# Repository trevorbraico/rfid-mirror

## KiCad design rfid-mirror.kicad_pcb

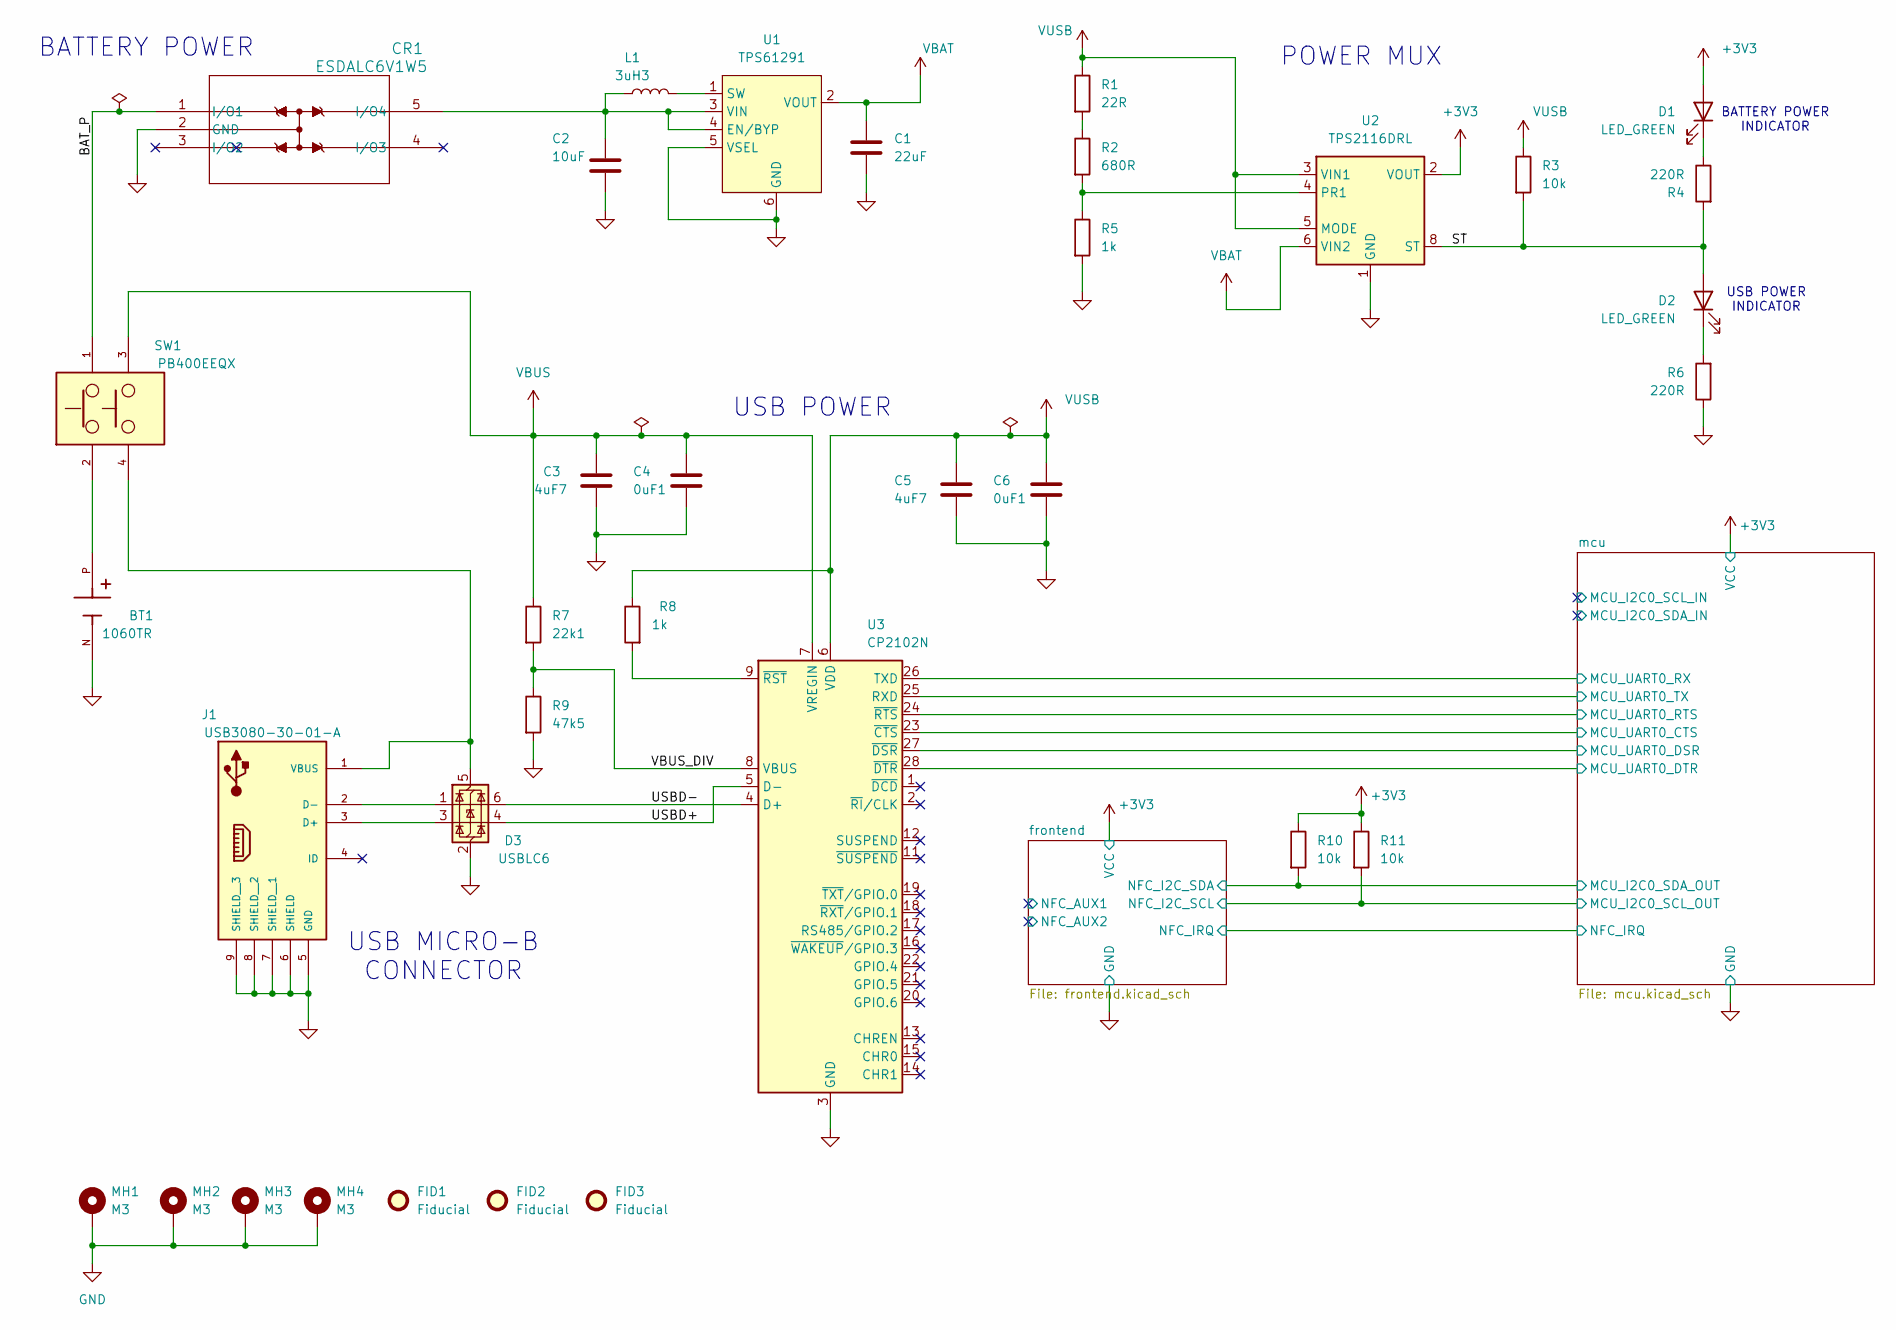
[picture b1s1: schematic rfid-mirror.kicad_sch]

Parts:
BT1: 1060TR; BAT_1060TR; PARTREV L; LCSC Part # C238069
C1: 22uF; C_0603_1608Metric; MPN CL10A226MP8NUNE; LCSC Part # C86295
C2: 10uF; C_0603_1608Metric; MPN CL10A106KP8NNNC; LCSC Part # C19702
C3, C5: 4uF7; C_0603_1608Metric; MPN CL10A475KO8NNNC; LCSC Part # C19666
C4, C6: 0uF1; C_0603_1608Metric; MPN CL10B104KB8NNNC; LCSC Part # C1591
CR1: ESDALC6V1W5; SOT323-5L_STM; MPN ESDALC6V1W5; LCSC Part # C703691
D1, D2: LED_GREEN; LED_0603_1608Metric; MPN SML-E12P8WT86; LCSC Part # C126319
D3: USBLC6; SOT-23-6; MPN USBLC6-2SC6; LCSC Part # C7519
FID1, FID2, FID3: Fiducial; Fiducial_1mm_Mask2mm
J1: USB3080-30-01-A; CONN5_80-30-01-A_GCT; MPN USB3080-30-01-A; LCSC Part # C6007479
L1: 3uH3; L_0603_1608Metric; MPN MLF1608A3R3KTA00; LCSC Part # C574026
MH1, MH2, MH3, MH4: M3; MountingHole_3.2mm_M3_Pad_Via
R1: 22R; R_0603_1608Metric; MPN RC0603FR-0722RL; LCSC Part # C107701
R2: 680R; R_0603_1608Metric; MPN RC0603FR-07680RL; LCSC Part # C112310
R3, R10, R11: 10k; R_0603_1608Metric; MPN RC0603FR-0710KL; LCSC Part # C98220
R4, R6: 220R; R_0603_1608Metric; MPN RC0603FR-07220RL; LCSC Part # C107696
R5, R8: 1k; R_0603_1608Metric; MPN RC0603JR-071KL; LCSC Part # C14676
R7: 22k1; R_0603_1608Metric; MPN RC0603FR-0722K1L; LCSC Part # C137768
R9: 47k5; R_0603_1608Metric; MPN RT0603BRE0747K5L; LCSC Part # C705859
SW1: PB400EEQX; SW_PB400EEQX; MPN PB400EEQX; LCSC Part # C5240796
U1: TPS61291; WSON-6-1EP_2x2mm_P0.65mm_EP1x1.6mm; MPN TPS61291DRVR; LCSC Part # C464809
U2: TPS2116DRL; SOT-583-8; MPN TPS2116DRLR; LCSC Part # C3235557
U3: CP2102N; QFN-28-1EP_5x5mm_P0.5mm_EP3.35x3.35mm; MPN CP2102N-A02-GQFN28R; LCSC Part # C964632

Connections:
+3V3: D1.2 (A), R10.1, R11.1, U2.2 (VOUT), U2.7 (VOUT); also elsewhere on the board
/BAT_P: CR1.1 (I/O1), SW1.1
/ST: D2.2 (A), R3.2, R4.1, U2.8 (ST)
/USBD+: D3.4 (I/O2), U3.5 (D-)
/USBD-: D3.6 (I/O1), U3.4 (D+)
/VBUS_DIV: R7.2, R9.1, U3.8 (VBUS)
/frontend/NFC_I2C_SCL: R11.2; also elsewhere on the board
/frontend/NFC_I2C_SDA: R10.2; also elsewhere on the board
/mcu/MCU_UART0_CTS: U3.23 (~CTS); also elsewhere on the board
/mcu/MCU_UART0_DSR: U3.27 (~DSR); also elsewhere on the board
/mcu/MCU_UART0_DTR: U3.28 (~DTR); also elsewhere on the board
/mcu/MCU_UART0_RTS: U3.24 (~RTS); also elsewhere on the board
/mcu/MCU_UART0_RX: U3.26 (TXD); also elsewhere on the board
/mcu/MCU_UART0_TX: U3.25 (RXD); also elsewhere on the board
GND: BT1.N, C1.2, C2.2, C3.2, C4.2, C5.2, C6.2, CR1.2 (GND), D3.2 (GND), J1.5 (GND), J1.6 (SHIELD), J1.7 (SHIELD__1), J1.8 (SHIELD__2), J1.9 (SHIELD__3), MH1.1, MH2.1, MH3.1, MH4.1, R5.2, R6.2, R9.2, U1.5 (VSEL), U1.6 (GND), U2.1 (GND), U3.3 (GND), U3.29 (GND); also elsewhere on the board
unnamed: BT1.P, SW1.2
unnamed: C2.1, CR1.5 (I/O4), L1.1, U1.3 (VIN), U1.4 (EN/BYP)
unnamed: D1.1 (K), R4.2
unnamed: D2.1 (K), R6.1
unnamed: D3.5 (VBUS), J1.1 (VBUS), SW1.4
unnamed: D3.3 (I/O2), J1.3 (D+)
unnamed: D3.1 (I/O1), J1.2 (D-)
unnamed: R1.2, R2.1
unnamed: L1.2, U1.1 (SW)
unnamed: R2.2, R5.1, U2.4 (PR1)
unnamed: R8.2, U3.9 (~RST)
VBAT: C1.1, U1.2 (VOUT), U2.6 (VIN2)
VBUS: C3.1, C4.1, R7.1, SW1.3, U3.7 (VREGIN)
VUSB: C5.1, C6.1, R1.1, R3.1, R8.1, U2.3 (VIN1), U2.5 (MODE), U3.6 (VDD)

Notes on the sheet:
POWER MUX
USB POWER
USB MICRO-B CONNECTOR
BATTERY POWER
USB POWER INDICATOR
BATTERY POWER INDICATOR

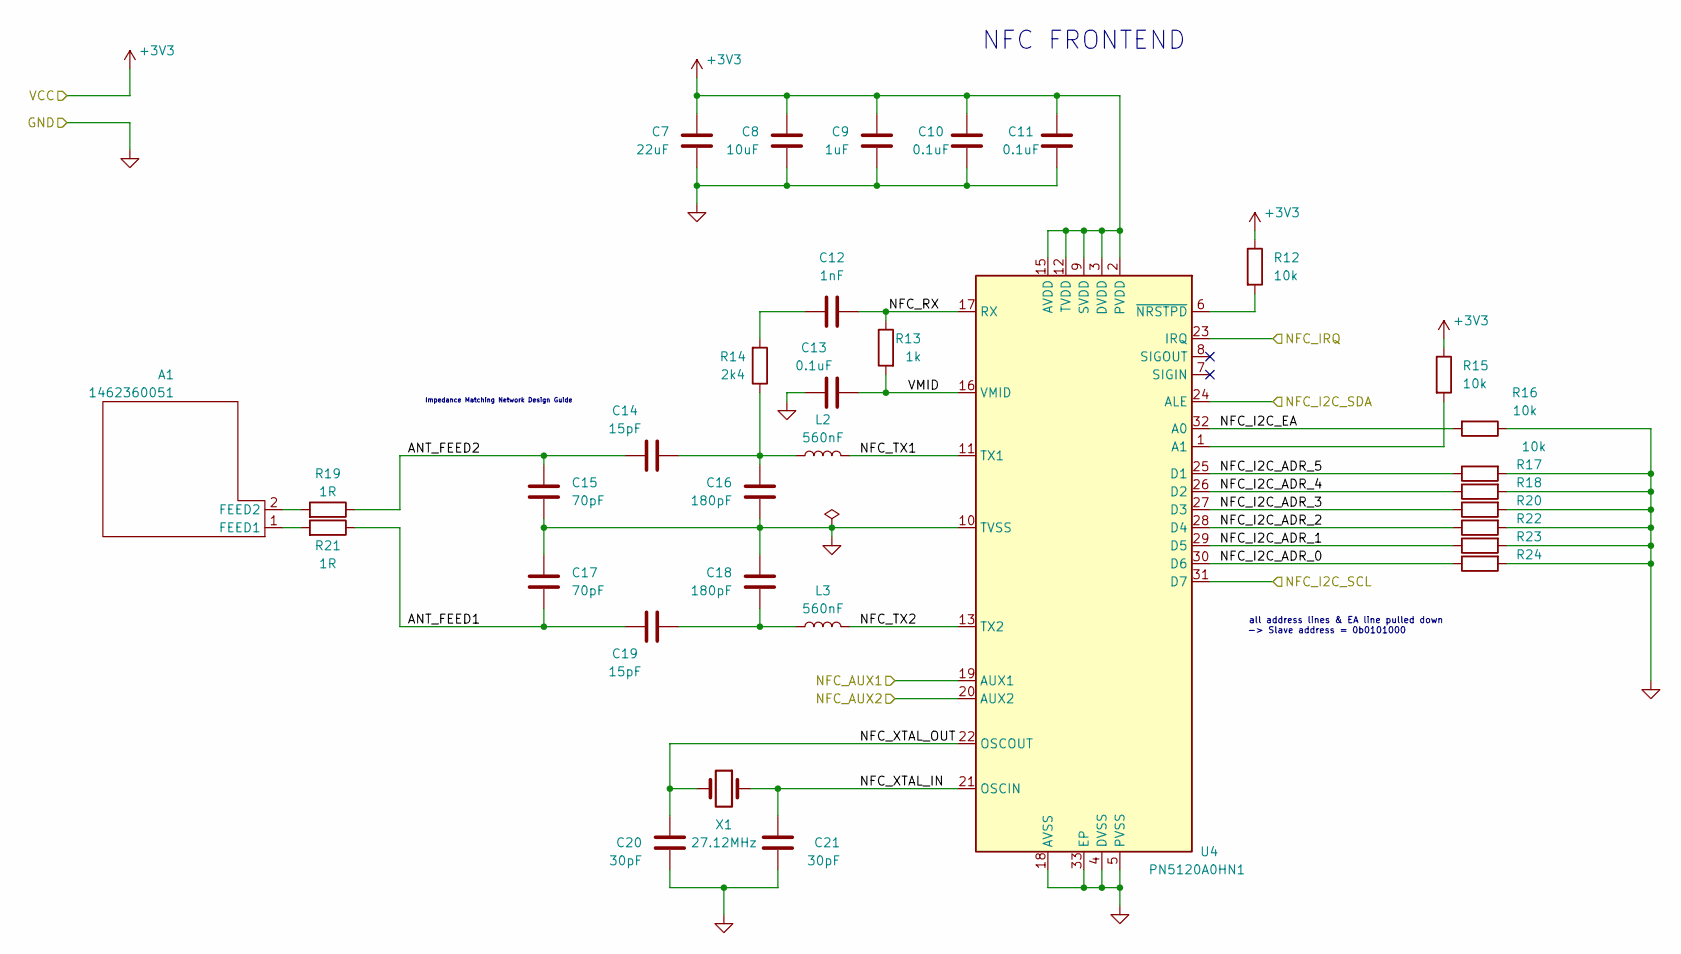
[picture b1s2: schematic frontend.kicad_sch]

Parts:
A1: 1462360051; 1462360101 RFID Antenna; MPN 1462360051; LCSC Part # C3284867
C7: 22uF; C_0603_1608Metric; MPN CL10A226MP8NUNE; LCSC Part # C86295
C8: 10uF; C_0603_1608Metric; MPN CL10A106KP8NNNC; LCSC Part # C19702
C9: 1uF; C_0603_1608Metric; MPN CL10A105KB8NNNC; LCSC Part # C15849
C10, C11, C13: 0.1uF; C_0603_1608Metric; MPN CL10B104KB8NNNC; LCSC Part # C1591
C12: 1nF; C_0603_1608Metric; MPN CL10C102JB8NNNC; LCSC Part # C163508
C14, C19: 15pF; C_0603_1608Metric; MPN CC0603GRNPO9BN150; LCSC Part # C519451
C15, C17: 70pF; C_0603_1608Metric; MPN MA0603CG700G500; LCSC Part # C3851853
C16, C18: 180pF; C_0603_1608Metric; MPN CC0603JRNPO9BN181; LCSC Part # C107041
C20, C21: 30pF; C_0603_1608Metric; MPN CC0603JRNPO9BN300; LCSC Part # C113797
L2, L3: 560nF; L_0603_1608Metric; MPN LQW18CNR56J00D; LCSC Part # C91630
R12, R15, R16, R17, R18, R20, R22, R23, R24: 10k; R_0603_1608Metric; MPN RC0603FR-0710KL; LCSC Part # C98220
R13: 1k; R_0603_1608Metric; MPN RC0603JR-071KL; LCSC Part # C14676
R14: 2k4; R_0603_1608Metric; MPN RC0603JR-072K4L; LCSC Part # C127450
R19, R21: 1R; R_0603_1608Metric; MPN RC0603JR-071RL; LCSC Part # C127987
U4: PN5120A0HN1; HVQFN-32-1EP_5x5mm_P0.5mm_EP3.1x3.1mm; MPN PN5120A0HN1/C2,151; LCSC Part # C38659
X1: 27.12MHz; Crystal_SMD_3225-4Pin_3.2x2.5mm; MPN XL2EL89CSI-111YLC-27.12M; LCSC Part # C5444554

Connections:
+3V3: C7.1, C8.1, C9.1, C10.1, C11.1, R12.1, R15.1, U4.2 (PVDD), U4.3 (DVDD), U4.9 (SVDD), U4.12 (TVDD), U4.15 (AVDD); also elsewhere on the board
/frontend/ANT_FEED1: C17.2, C19.1, R21.1
/frontend/ANT_FEED2: C14.1, C15.1, R19.1
/frontend/NFC_AUX1: U4.19 (AUX1)
/frontend/NFC_AUX2: U4.20 (AUX2)
/frontend/NFC_I2C_ADR_0: R24.1, U4.30 (D6)
/frontend/NFC_I2C_ADR_1: R23.1, U4.29 (D5)
/frontend/NFC_I2C_ADR_2: R22.1, U4.28 (D4)
/frontend/NFC_I2C_ADR_3: R20.1, U4.27 (D3)
/frontend/NFC_I2C_ADR_4: R18.1, U4.26 (D2)
/frontend/NFC_I2C_ADR_5: R17.1, U4.25 (D1)
/frontend/NFC_I2C_EA: R16.2, U4.32 (A0)
/frontend/NFC_I2C_SCL: U4.31 (D7); also elsewhere on the board
/frontend/NFC_I2C_SDA: U4.24 (ALE); also elsewhere on the board
/frontend/NFC_IRQ: U4.23 (IRQ); also elsewhere on the board
/frontend/NFC_RX: C12.1, R13.1, U4.17 (RX)
/frontend/NFC_TX1: L2.1, U4.11 (TX1)
/frontend/NFC_TX2: L3.1, U4.13 (TX2)
/frontend/NFC_XTAL_IN: C21.1, U4.21 (OSCIN), X1.1
/frontend/NFC_XTAL_OUT: C20.1, U4.22 (OSCOUT), X1.2
/frontend/VMID: C13.1, R13.2, U4.16 (VMID)
GND: C7.2, C8.2, C9.2, C10.2, C11.2, C13.2, C15.2, C16.2, C17.1, C18.1, C20.2, C21.2, R16.1, R17.2, R18.2, R20.2, R22.2, R23.2, R24.2, U4.4 (DVSS), U4.5 (PVSS), U4.10 (TVSS), U4.18 (AVSS), U4.33 (EP); also elsewhere on the board
unnamed: A1.1 (FEED1), R21.2
unnamed: A1.2 (FEED2), R19.2
unnamed: C12.2, R14.2
unnamed: C14.2, C16.1, L2.2, R14.1
unnamed: C18.2, C19.2, L3.2
unnamed: R15.2, U4.1 (A1)
unnamed: R12.2, U4.6 (~NRSTPD)

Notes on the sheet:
all address lines & EA line pulled down -> Slave address = 0b0101000
Impedance Matching Network Design Guide
NFC FRONTEND

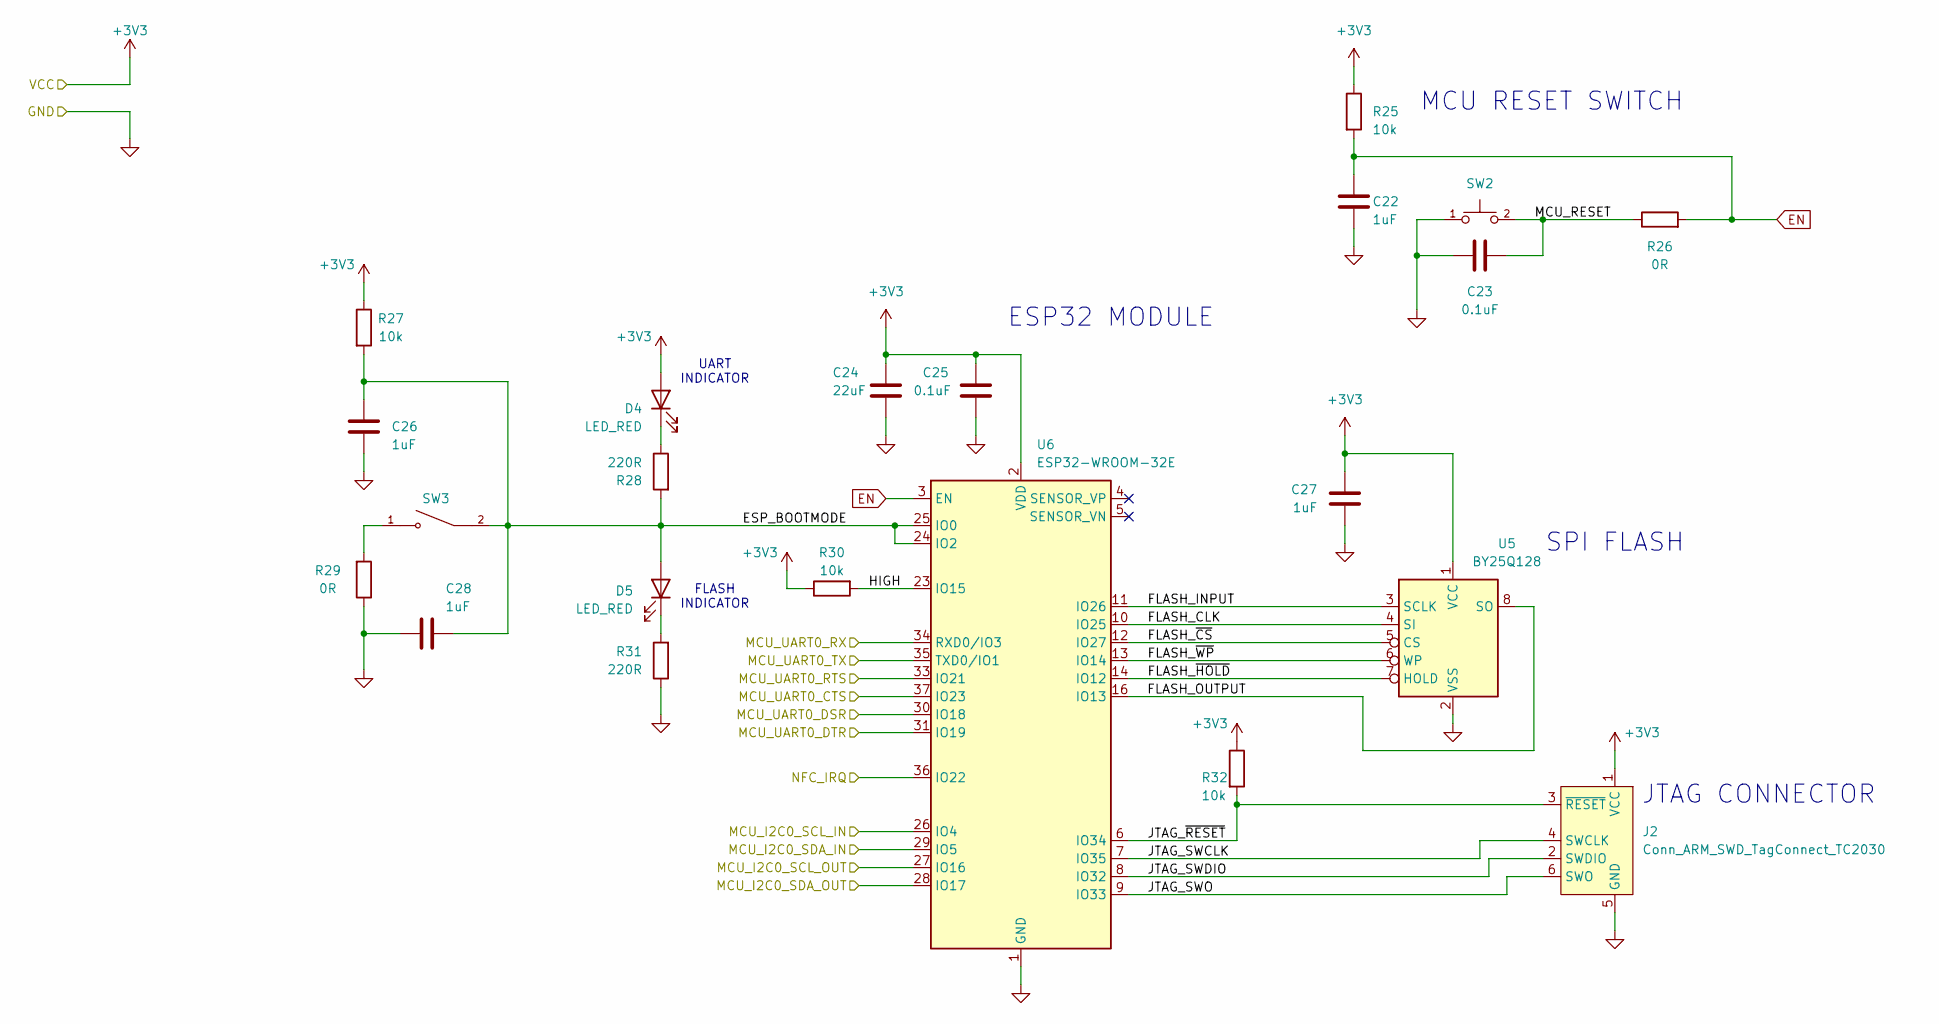
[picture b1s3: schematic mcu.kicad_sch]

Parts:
C22, C26, C27, C28: 1uF; C_0603_1608Metric; MPN CL10A105KB8NNNC; LCSC Part # C15849
C23, C25: 0.1uF; C_0603_1608Metric; MPN CL10B104KB8NNNC; LCSC Part # C1591
C24: 22uF; C_0603_1608Metric; MPN CL10A226MP8NUNE; LCSC Part # C86295
D4, D5: LED_RED; LED_0603_1608Metric; MPN SML-D12U8WT86C; LCSC Part # C2846640
J2: Conn_ARM_SWD_TagConnect_TC2030; Tag-Connect_TC2030-IDC-FP_2x03_P1.27mm_Vertical
R25, R27, R30, R32: 10k; R_0603_1608Metric; MPN RC0603FR-0710KL; LCSC Part # C98220
R26, R29: 0R; R_0603_1608Metric; MPN RC0603JR-070RL; LCSC Part # C105580
R28, R31: 220R; R_0603_1608Metric; MPN RC0603FR-07220RL; LCSC Part # C107696
SW2: B3U-1000P; SW_B3U-1000P; MPN B3U-1000P; LCSC Part # C231329
SW3: GF-123-0054; SW_GF-123-0054; MPN GF-123-0054; LCSC Part # C3029861
U5: BY25Q128; SOIC-8_5.3x5.3mm_P1.27mm; MPN BY25Q128ESSIG(T); LCSC Part # C22471255
U6: ESP32-WROOM-32E; MPN ESP32-WROOM-32E-N4; LCSC Part # C701341

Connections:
+3V3: C24.1, C25.1, C27.1, D4.2 (A), J2.1 (VCC), R25.1, R27.1, R30.1, R32.1, U5.1 (VCC), U6.2 (VDD); also elsewhere on the board
/frontend/NFC_I2C_SCL: U6.27 (IO16); also elsewhere on the board
/frontend/NFC_I2C_SDA: U6.28 (IO17); also elsewhere on the board
/frontend/NFC_IRQ: U6.36 (IO22); also elsewhere on the board
/mcu/ESP_BOOTMODE: C26.1, C28.2, D5.2 (A), R27.2, R28.1, SW3.2, U6.24 (IO2), U6.25 (IO0)
/mcu/FLASH_CLK: U5.4 (SI), U6.10 (IO25)
/mcu/FLASH_INPUT: U5.3 (SCLK), U6.11 (IO26)
/mcu/FLASH_OUTPUT: U5.8 (SO), U6.16 (IO13)
/mcu/FLASH_~CS: U5.5 (CS), U6.12 (IO27)
/mcu/FLASH_~HOLD: U5.7 (HOLD), U6.14 (IO12)
/mcu/FLASH_~WP: U5.6 (WP), U6.13 (IO14)
/mcu/HIGH: R30.2, U6.23 (IO15)
/mcu/JTAG_SWCLK: J2.4 (SWCLK), U6.7 (IO35)
/mcu/JTAG_SWDIO: J2.2 (SWDIO), U6.8 (IO32)
/mcu/JTAG_SWO: J2.6 (SWO), U6.9 (IO33)
/mcu/JTAG_~RESET: J2.3 (~RESET), R32.2, U6.6 (IO34)
/mcu/MCU_I2C0_SCL_IN: U6.26 (IO4)
/mcu/MCU_I2C0_SDA_IN: U6.29 (IO5)
/mcu/MCU_RESET: C23.1, R26.1, SW2.2
/mcu/MCU_UART0_CTS: U6.37 (IO23); also elsewhere on the board
/mcu/MCU_UART0_DSR: U6.30 (IO18); also elsewhere on the board
/mcu/MCU_UART0_DTR: U6.31 (IO19); also elsewhere on the board
/mcu/MCU_UART0_RTS: U6.33 (IO21); also elsewhere on the board
/mcu/MCU_UART0_RX: U6.34 (RXD0/IO3); also elsewhere on the board
/mcu/MCU_UART0_TX: U6.35 (TXD0/IO1); also elsewhere on the board
EN: C22.1, R25.2, R26.2, U6.3 (EN)
GND: C22.2, C23.2, C24.2, C25.2, C26.2, C27.2, C28.1, J2.5 (GND), R29.1, R31.2, SW2.1, U5.2 (VSS), U6.1 (GND), U6.15 (GND), U6.38 (GND), U6.39 (GND); also elsewhere on the board
unnamed: D4.1 (K), R28.2
unnamed: D5.1 (K), R31.1
unnamed: R29.2, SW3.1

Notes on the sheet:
SPI FLASH
UART INDICATOR
MCU RESET SWITCH
ESP32 MODULE
JTAG CONNECTOR
FLASH INDICATOR

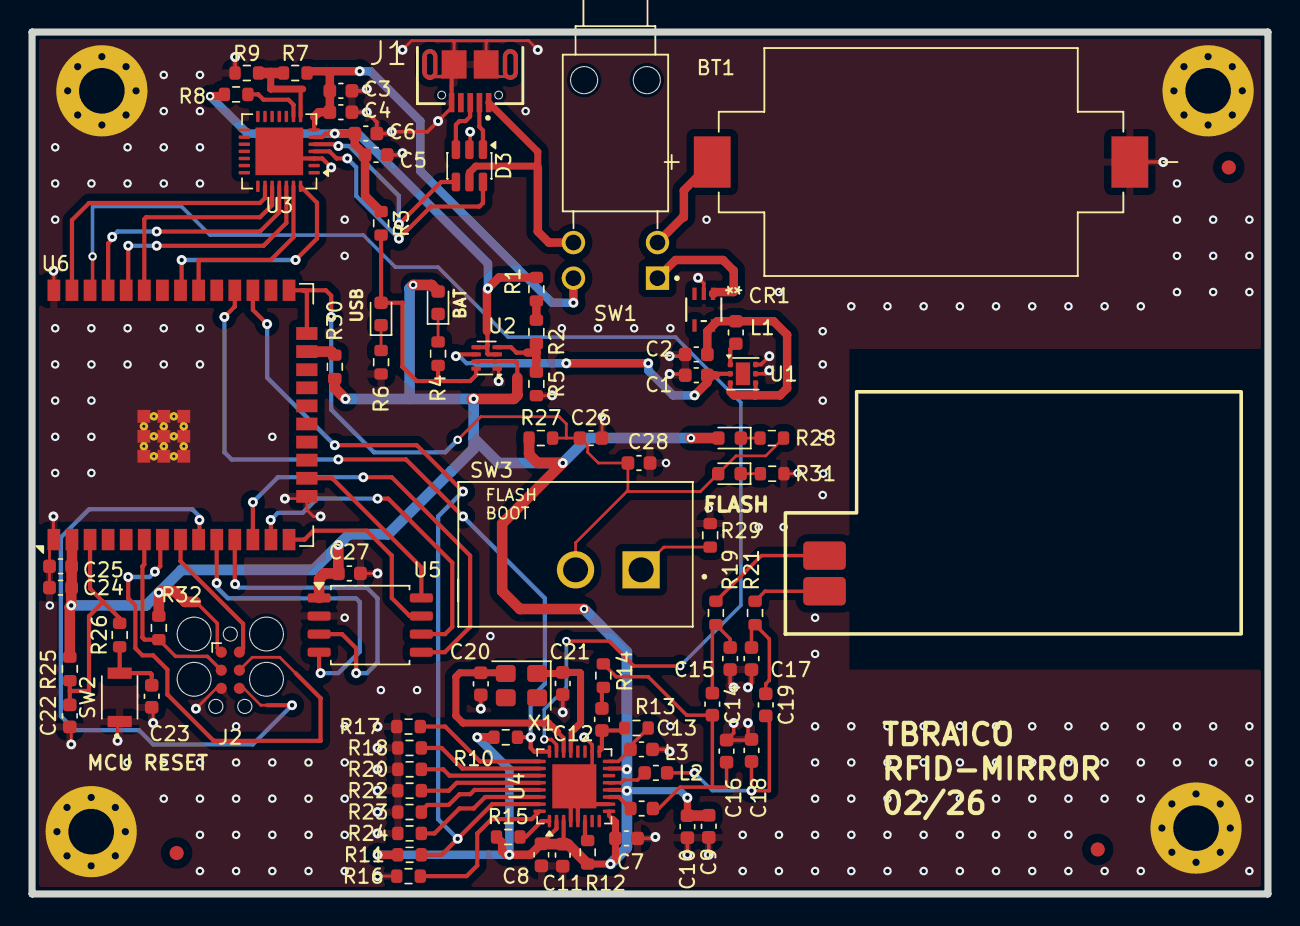
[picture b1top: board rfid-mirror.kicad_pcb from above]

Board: 2 copper layers, 86.8 x 60.5 mm, 90 parts (0 on the bottom side), 69 nets.

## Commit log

2026-03-03 new stuff
